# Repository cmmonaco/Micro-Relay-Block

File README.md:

# Micro Relay Block

This a simple carrier board for a micro relay used to switch a high voltage DC load with a microcontroller. The board was designed for use with an Omron G5V-1 relay which allows switching control of loads up to 60V and 1A from a 3.3V controller. 

## Schematic

The relay coil is switched using a NPN transistor. When the load is switched on, the an LED indicates the relay is active.

## PCB

The board was designed in EAGLE and fabricated by [Oshpark](http://oshpark.com).

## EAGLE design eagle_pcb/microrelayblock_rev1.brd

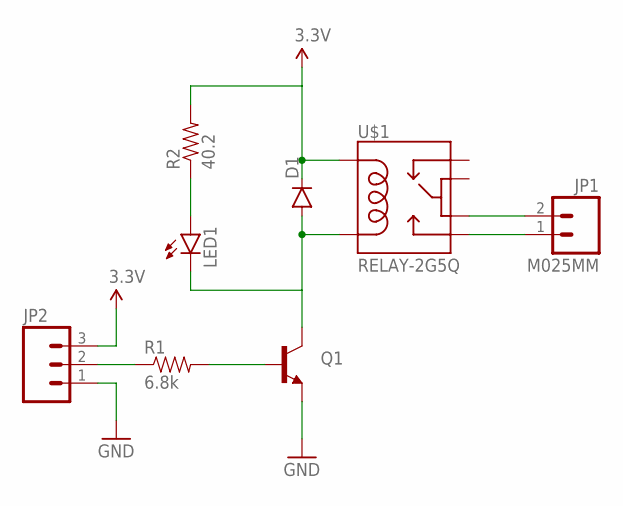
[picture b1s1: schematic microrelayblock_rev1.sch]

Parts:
D1: DIODESMA-KIT; SMA-DIODE-KIT
JP1: M025MM; SCREWTERMINAL-5MM-2
JP2: M03SCREW; SCREWTERMINAL-3.5MM-3
LED1: LED0603; LED-0603
Q1: TRANSISTOR_NPNSOT23; SOT23
R1: 6.8k; 0805
R2: 40.2; 0805
U$1: RELAY-2G5Q; RELAY-G5V

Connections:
3.3V: D1.C, JP2.3, R2.2, U$1.2
GND: JP2.1, Q1.2 (E)
unnamed: Q1.1 (B), R1.2
unnamed: D1.A, LED1.C, Q1.3 (C), U$1.9
unnamed: JP1.1, U$1.10
unnamed: JP1.2, U$1.6
unnamed: LED1.A, R2.1
unnamed: JP2.2, R1.1

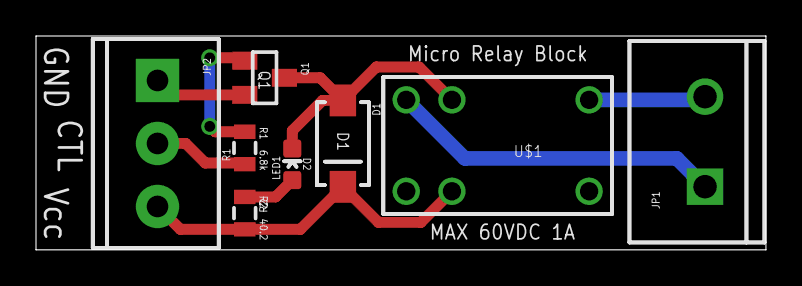
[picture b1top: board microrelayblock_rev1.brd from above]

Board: 2 copper layers, 40.6 x 11.9 mm, 8 parts (0 on the bottom side), 8 nets.

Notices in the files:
parts and their libraries:
SparkFun-DiscreteSemi: Licensing: Creative Commons ShareAlike 4.0 International - https://creativecommons.org/licenses/by-sa/4.0
